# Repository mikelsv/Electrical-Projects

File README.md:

# Electrical-Projects
Projects based on electronic components and 3d printed models

## KronaDevice -  Version 1.2 (16.12.2023)
Krona device. StepUp dc-dc converter from 3.7v to 9v. For tester DT830.

### Sources:
KiCad sheme: /kicad/StepUp 3_7 to 9 MC34063

Openscad: /openscad/Voltage convertor/StepUp MC34063 3_7 to 9v.scad

Thingiverse: https://www.thingiverse.com/thing:6368927

YouTube: https://www.youtube.com/watch?v=WVIPYxtIsH8

Pikabu: https://pikabu.ru/story/vechnaya_krona_dlya_testera_dt830_10916306

## Power Supply XL4015
Power supply based on the XL4015 module.

### Sources:
Technical info: https://docs.google.com/spreadsheets/d/1Mg476g0cRaEf-cvwi_3nTZD_-khxy4uZv7GkhRPRcu0/edit?usp=sharing

Presentation: https://docs.google.com/presentation/d/1VEQzsRly4vlJmZFCTP_CDkUu1_kLX7wChvYJrdol7VE/edit?usp=sharing

Thingiverse: https://www.thingiverse.com/thing:6388327

Openscad: /openscad/Voltage convertor/Power Supply XL4015.scad

YouTube: https://youtu.be/f8i39ENs2dU

## Electronic Load

### Sources:
KiCad sheme: /kicad/Electronic Load 2N5401 2N5551

Openscad: /openscad/Voltage convertor/Electronic Load 2N5401 2N5551.scad

YouTube: https://youtu.be/1Vz2KkpufGk

## Human Acupuncture Tester

### Sources:
KiCad sheme: /kicad/Human Acu Tester

Openscad: /openscad/Voltage convertor/Human Acu Tester.scad

YouTube: https://youtube.com/shorts/WKZl-tUxw0U

Pikabu: https://pikabu.ru/story/yelektro_akupunktura_11068489

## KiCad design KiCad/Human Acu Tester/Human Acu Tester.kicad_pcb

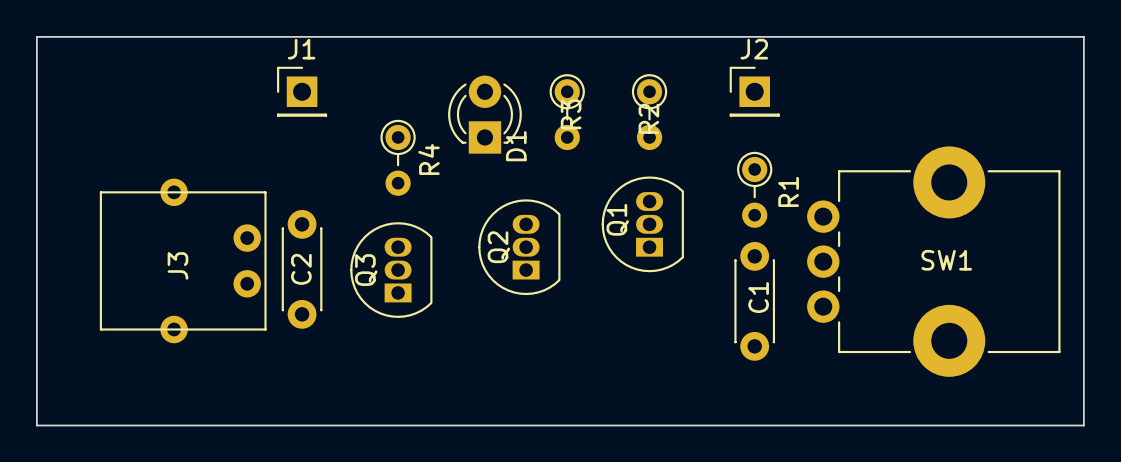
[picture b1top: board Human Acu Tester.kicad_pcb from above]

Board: 2 copper layers, 58.2 x 21.6 mm, 14 parts (0 on the bottom side), 10 nets, no tracks yet.

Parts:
C1: 22nF; C_Disc_D4.3mm_W1.9mm_P5.00mm
C2: 10uF; C_Disc_D4.3mm_W1.9mm_P5.00mm
D1: LED; LED_D3.0mm
J1: Human +; PinHeader_1x01_P2.54mm_Vertical
J2: Human -; PinHeader_1x01_P2.54mm_Vertical
J3: USB_B_Micro; USB_Micro_Ali-2Pin
Q1, Q2, Q3: 2N2222; TO-92_Inline
R1: 10k; R_Axial_DIN0204_L3.6mm_D1.6mm_P2.54mm_Vertical
R2: 10K; R_Axial_DIN0204_L3.6mm_D1.6mm_P2.54mm_Vertical
R3: 1K; R_Axial_DIN0204_L3.6mm_D1.6mm_P2.54mm_Vertical
R4: 680R; R_Axial_DIN0204_L3.6mm_D1.6mm_P2.54mm_Vertical
SW1: 200K; Potentiometer_Alps_RK09K_Single_Vertical

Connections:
unnamed: C1.1, Q1.2, R1.2, SW1.3
unnamed: C1.2, C2.2, J3.5, Q3.1, SW1.2
unnamed: C2.1, D1.2, J1.1, J3.1, R2.1, R3.1
unnamed: D1.1, R4.1
unnamed: J2.1, R1.1
unnamed: Q1.1, Q2.2
unnamed: Q1.3, R2.2
unnamed: Q2.1, Q3.2
unnamed: Q2.3, R3.2
unnamed: Q3.3, R4.2

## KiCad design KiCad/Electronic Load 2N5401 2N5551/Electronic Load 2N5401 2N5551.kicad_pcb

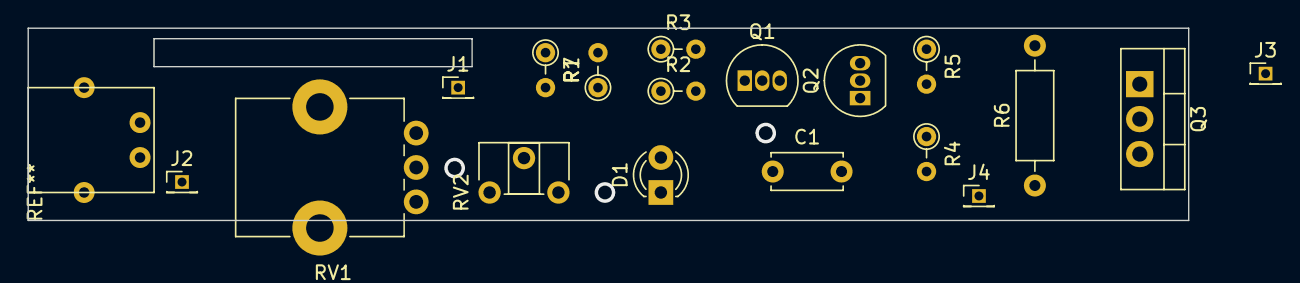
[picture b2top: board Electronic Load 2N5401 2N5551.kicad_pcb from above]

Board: 2 copper layers, 84.3 x 14.0 mm, 18 parts (0 on the bottom side), 11 nets, no tracks yet.

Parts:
C1: 1uF; C_Disc_D5.0mm_W2.5mm_P5.00mm
D1: LED; LED_D3.0mm
J1: 12V; PinHeader_1x01_P1.27mm_Vertical
J2, J4: GND; PinHeader_1x01_P1.27mm_Vertical
J3: 0-50V; PinHeader_1x01_P1.27mm_Vertical
Q1: 2N5401; TO-92_Inline
Q2: 2N5551; TO-92_Inline
Q3: IRF530N; TO-220-3_Vertical
R1, R3, R4: 220K; R_Axial_DIN0204_L3.6mm_D1.6mm_P2.54mm_Vertical
R2: 20K; R_Axial_DIN0204_L3.6mm_D1.6mm_P2.54mm_Vertical
R5: 1K; R_Axial_DIN0204_L3.6mm_D1.6mm_P2.54mm_Vertical
R6: 0.15R; R_Axial_DIN0207_L6.3mm_D2.5mm_P10.16mm_Horizontal
R7: 2.2K; R_Axial_DIN0204_L3.6mm_D1.6mm_P2.54mm_Vertical
RV1: 10K; Potentiometer_Alps_RK09K_Single_Vertical
RV2: 5K; Potentiometer_ACP_CA6-H2,5_Horizontal

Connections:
+12V: J1.1, R1.1, R2.1, R3.1, R7.2
GND: C1.2, D1.1, J2.1, J4.1, Q2.1, R4.2, R6.1, RV2.2, RV2.3
unnamed: C1.1, Q1.2, RV1.2
unnamed: D1.2, R7.1
unnamed: J3.1, Q3.2
unnamed: Q1.1, R2.2, R5.2
unnamed: Q1.3, Q2.2, R4.1
unnamed: Q2.3, Q3.1, R3.2
unnamed: Q3.3, R5.1, R6.2
unnamed: R1.2, RV1.1
unnamed: RV1.3, RV2.1

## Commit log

2023-12-15 Begin
2023-12-16 Fix folder name
2024-01-08 Electronic Load project
2024-01-27 Human Acupuncture Tester
